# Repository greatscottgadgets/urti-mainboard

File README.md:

# URTI Mainboard

This is the open source hardware design for the mainboard of URTI, the Universal Radio Test Instrument.

https://greatscottgadgets.com/urti/

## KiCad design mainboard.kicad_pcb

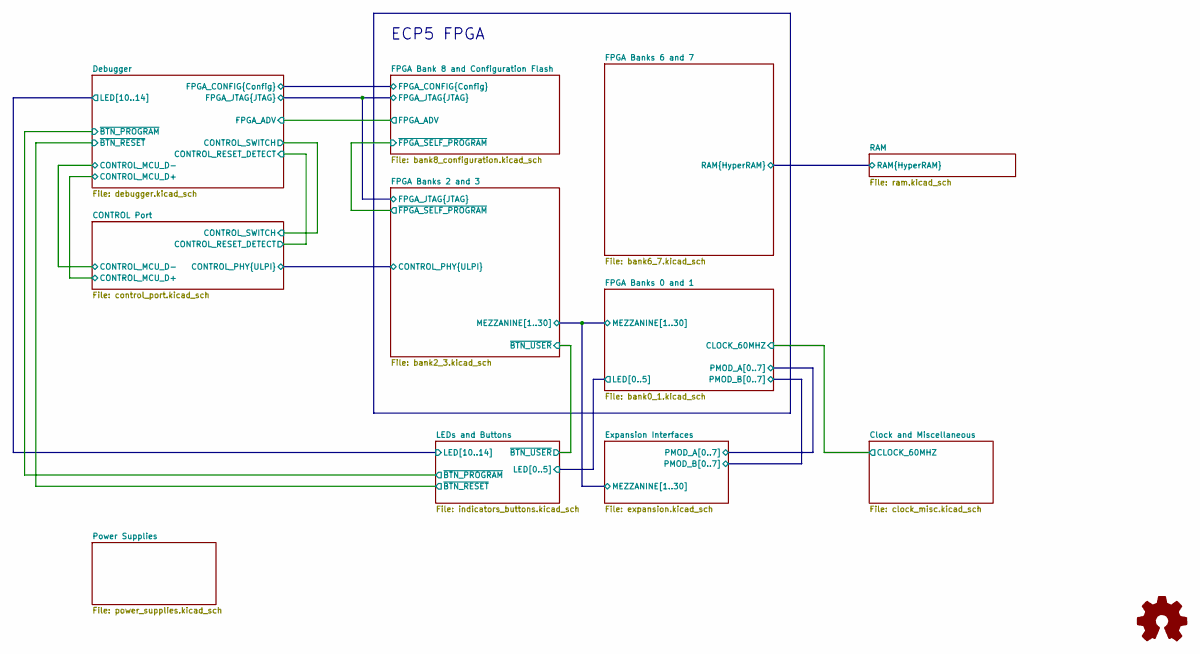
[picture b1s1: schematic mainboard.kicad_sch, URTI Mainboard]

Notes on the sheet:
ECP5 FPGA

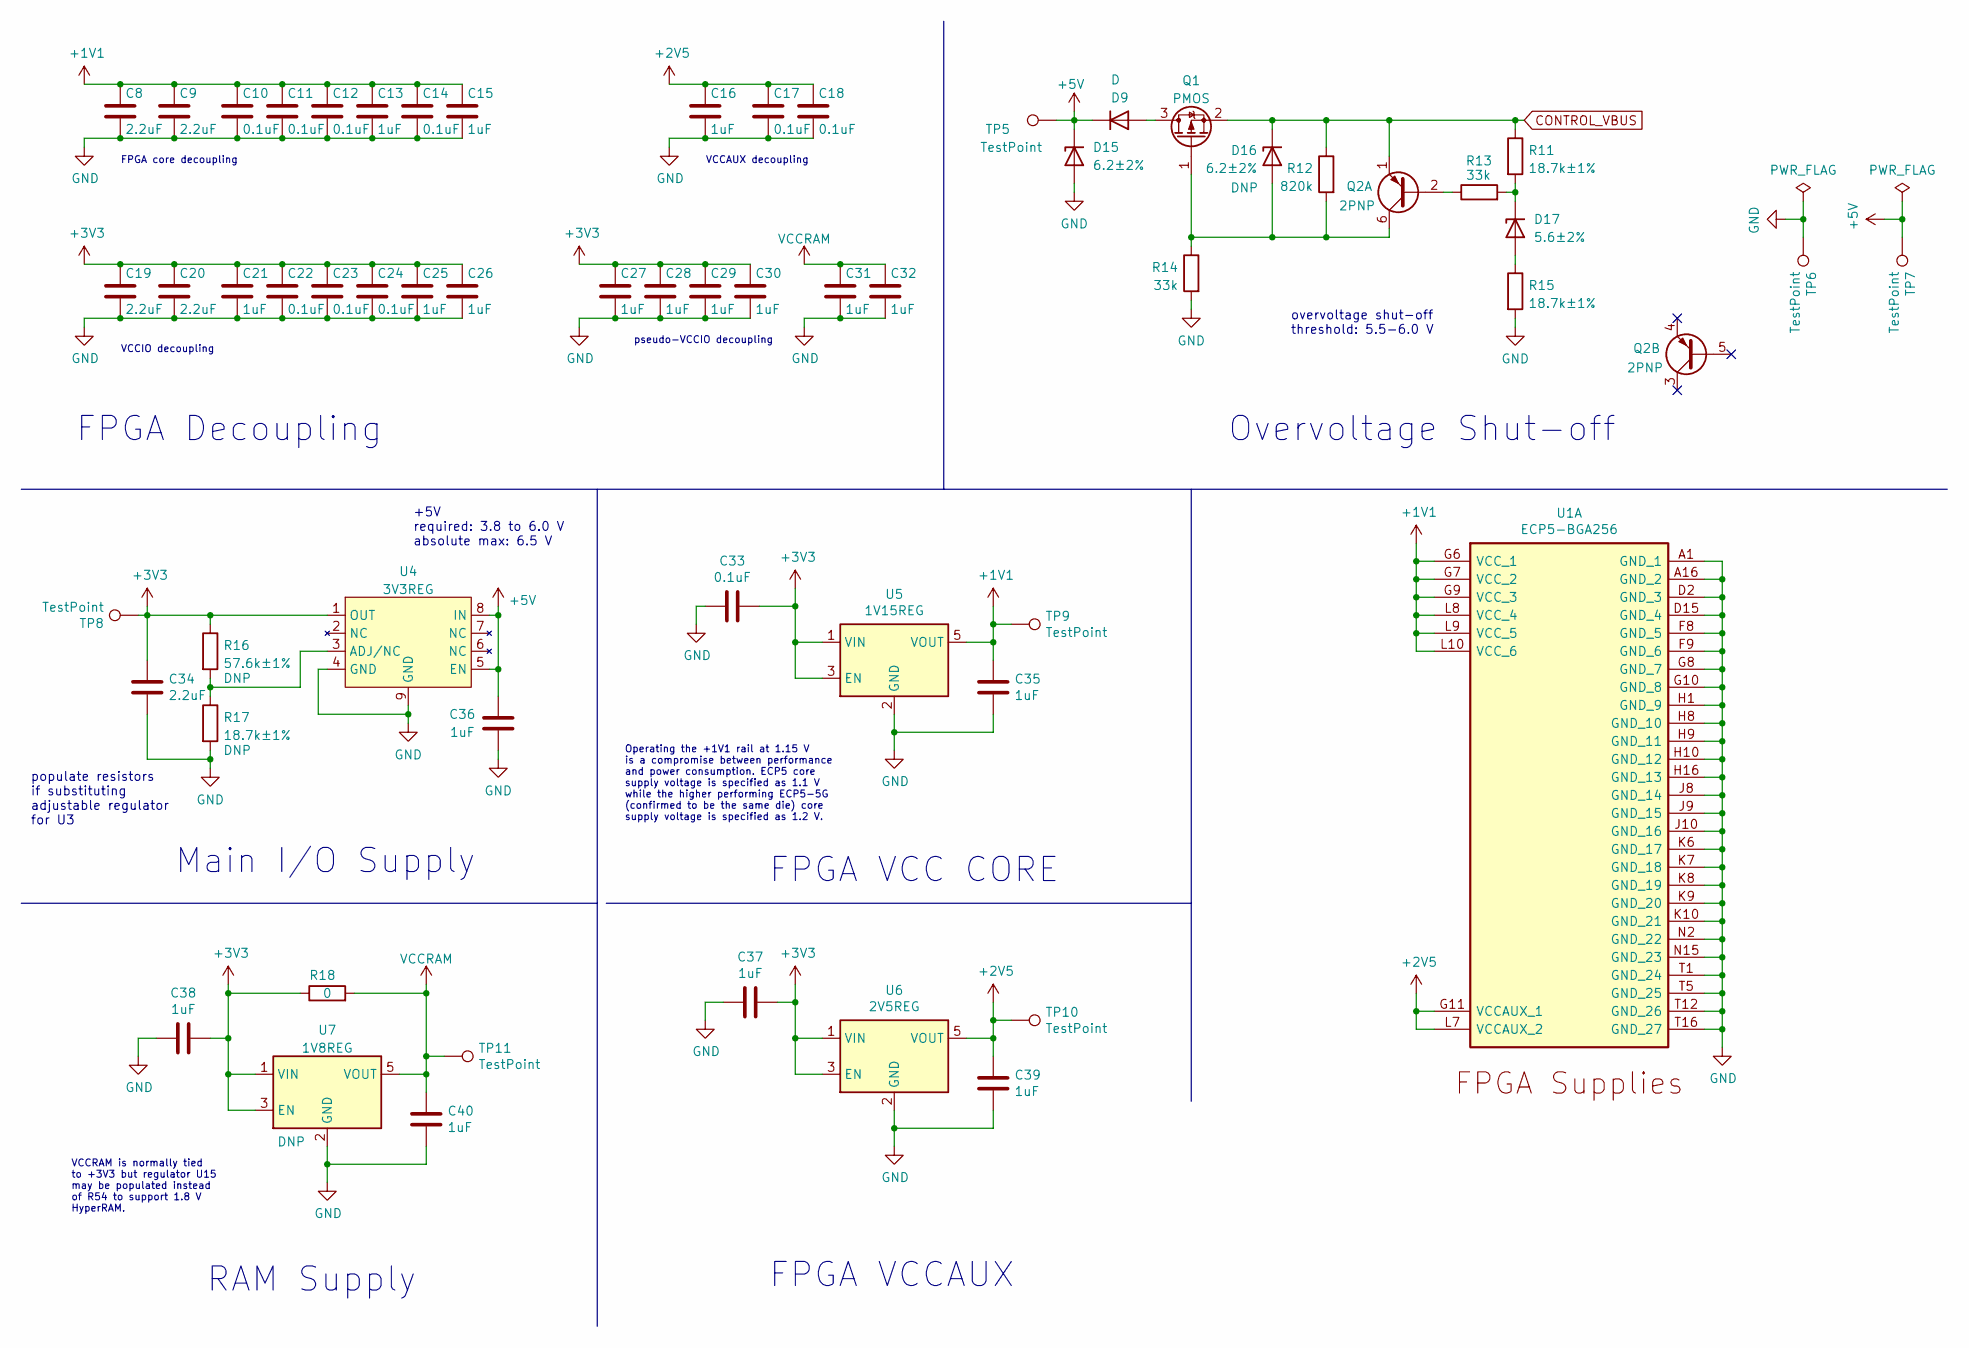
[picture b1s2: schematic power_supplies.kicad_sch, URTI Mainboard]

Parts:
C8, C9, C19, C20, C34: 2.2uF; C_0603_1608Metric; Part Number CL10A225KP8NNNC
C10, C11, C12, C14, C17, C18, C22, C23, C24, C33: 0.1uF; C_0402_1005Metric; Part Number CL05A104KA5NNNC
C13, C15, C16, C21, C25, C26, C27, C28, C29, C30, C31, C32, C35, C36, C37, C38, C39, C40: 1uF; C_0402_1005Metric; Part Number CL05A105MQ5NNNC
D9: D; D_SOD-123FL; Part Number U1D
D15, D16: 6.2±2%; DFN1006-2; Part Number BZX884-B6V2,315
D17: 5.6±2%; DFN1006-2; Part Number BZX884-B5V6,315
Q1: PMOS; SOT-23-3; Part Number YJL3401A
Q2: 2PNP; SOT-363_SC-70-6; Part Number BC857BS
R11, R15, R17: 18.7k±1%; R_0402_1005Metric; Part Number ERJ-2RKF1872X
R12: 820k; R_0402_1005Metric; Part Number RC0402JR-07820KL
R13, R14: 33k; R_0402_1005Metric; Part Number ERJ-2GEJ333X
R16: 57.6k±1%; R_0402_1005Metric; Part Number RC0402FR-0757K6L
R18: 0; R_0402_1005Metric; Part Number RC0402FR-070RL
TP5, TP6, TP7, TP8, TP9, TP10, TP11: TestPoint; TestPoint_Pad_D1.0mm
U1: ECP5-BGA256; lattice_cabga256; Part Number LFE5U-12F-6BG256C
U4: 3V3REG; DFN-8-1EP_3x3mm_P0.65mm_EP1.55x2.4mm; Part Number AP7361EA-33FGE-7
U5: 1V15REG; SOT-23-5; Part Number TCR2EF115,LM(CT
U6: 2V5REG; SOT-23-5; Part Number MIC5504-2.5YM5-TR
U7: 1V8REG; SOT-23-5; Part Number MIC5504-1.8YM5-TR

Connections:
+1V1: C8.1, C9.1, C10.1, C11.1, C12.1, C13.1, C14.1, C15.1, C35.1, TP9.1, U1.G6 (VCC_1), U1.G7 (VCC_2), U1.G9 (VCC_3), U1.L8 (VCC_4), U1.L9 (VCC_5), U1.L10 (VCC_6), U5.5 (VOUT)
+2V5: C16.1, C17.1, C18.1, C39.1, TP10.1, U1.G11 (VCCAUX_1), U1.L7 (VCCAUX_2), U6.5 (VOUT)
+3V3: C19.1, C20.1, C21.1, C22.1, C23.1, C24.1, C25.1, C26.1, C27.1, C28.1, C29.1, C30.1, C33.1, C34.1, C37.1, C38.1, R16.1, R18.1, TP8.1, U4.1 (OUT), U5.1 (VIN), U5.3 (EN), U6.1 (VIN), U6.3 (EN), U7.1 (VIN), U7.3 (EN); also elsewhere on the board
+5V: C36.1, D9.1 (K), D15.1 (K), TP5.1, TP7.1, U4.5 (EN), U4.8 (IN); also elsewhere on the board
CONTROL_VBUS: D16.1 (K), Q1.2 (S), Q2.1 (E1), R11.1, R12.1; also elsewhere on the board
GND: C8.2, C9.2, C10.2, C11.2, C12.2, C13.2, C14.2, C15.2, C16.2, C17.2, C18.2, C19.2, C20.2, C21.2, C22.2, C23.2, C24.2, C25.2, C26.2, C27.2, C28.2, C29.2, C30.2, C31.2, C32.2, C33.2, C34.2, C35.2, C36.2, C37.2, C38.2, C39.2, C40.2, D15.2 (A), R14.2, R15.2, R17.2, TP6.1, U1.A1 (GND_1), U1.A16 (GND_2), U1.D2 (GND_3), U1.D15 (GND_4), U1.F8 (GND_5), U1.F9 (GND_6), U1.G8 (GND_7), U1.G10 (GND_8), U1.H1 (GND_9), U1.H8 (GND_10), U1.H9 (GND_11), U1.H10 (GND_12), U1.H16 (GND_13), U1.J8 (GND_14), U1.J9 (GND_15), U1.J10 (GND_16), U1.K6 (GND_17), U1.K7 (GND_18), U1.K8 (GND_19), U1.K9 (GND_20), U1.K10 (GND_21), U1.N2 (GND_22), U1.N15 (GND_23), U1.T1 (GND_24), U1.T5 (GND_25), U1.T12 (GND_26), U1.T16 (GND_27), U4.4 (GND), U4.9 (GND), U5.2 (GND), U6.2 (GND), U7.2 (GND); also elsewhere on the board
unnamed: D9.2 (A), Q1.3 (D)
unnamed: D16.2 (A), Q1.1 (G), Q2.6 (C1), R12.2, R14.1
unnamed: D17.2 (A), R15.1
unnamed: D17.1 (K), R11.2, R13.2
unnamed: Q2.2 (B1), R13.1
unnamed: R16.2, R17.1, U4.3 (ADJ/NC)
VCCRAM: C31.1, C32.1, C40.1, R18.2, TP11.1, U7.5 (VOUT); also elsewhere on the board

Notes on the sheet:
VCCIO decoupling
FPGA VCC CORE
FPGA Decoupling
FPGA core decoupling
+5V required: 3.8 to 6.0 V absolute max: 6.5 V
overvoltage shut-off threshold: 5.5-6.0 V
VCCRAM is normally tied to +3V3 but regulator U15 may be populated instead of R54 to support 1.8 V HyperRAM.
VCCAUX decoupling
FPGA VCCAUX
Main I/O Supply
Overvoltage Shut-off
populate resistors if substituting adjustable regulator for U3
RAM Supply
Operating the +1V1 rail at 1.15 V is a compromise between performance and power consumption. ECP5 core supply voltage is specified as 1.1 V while the higher performing ECP5-5G (confirmed to be the same die) core supply voltage is specified as 1.2 V.
pseudo-VCCIO decoupling

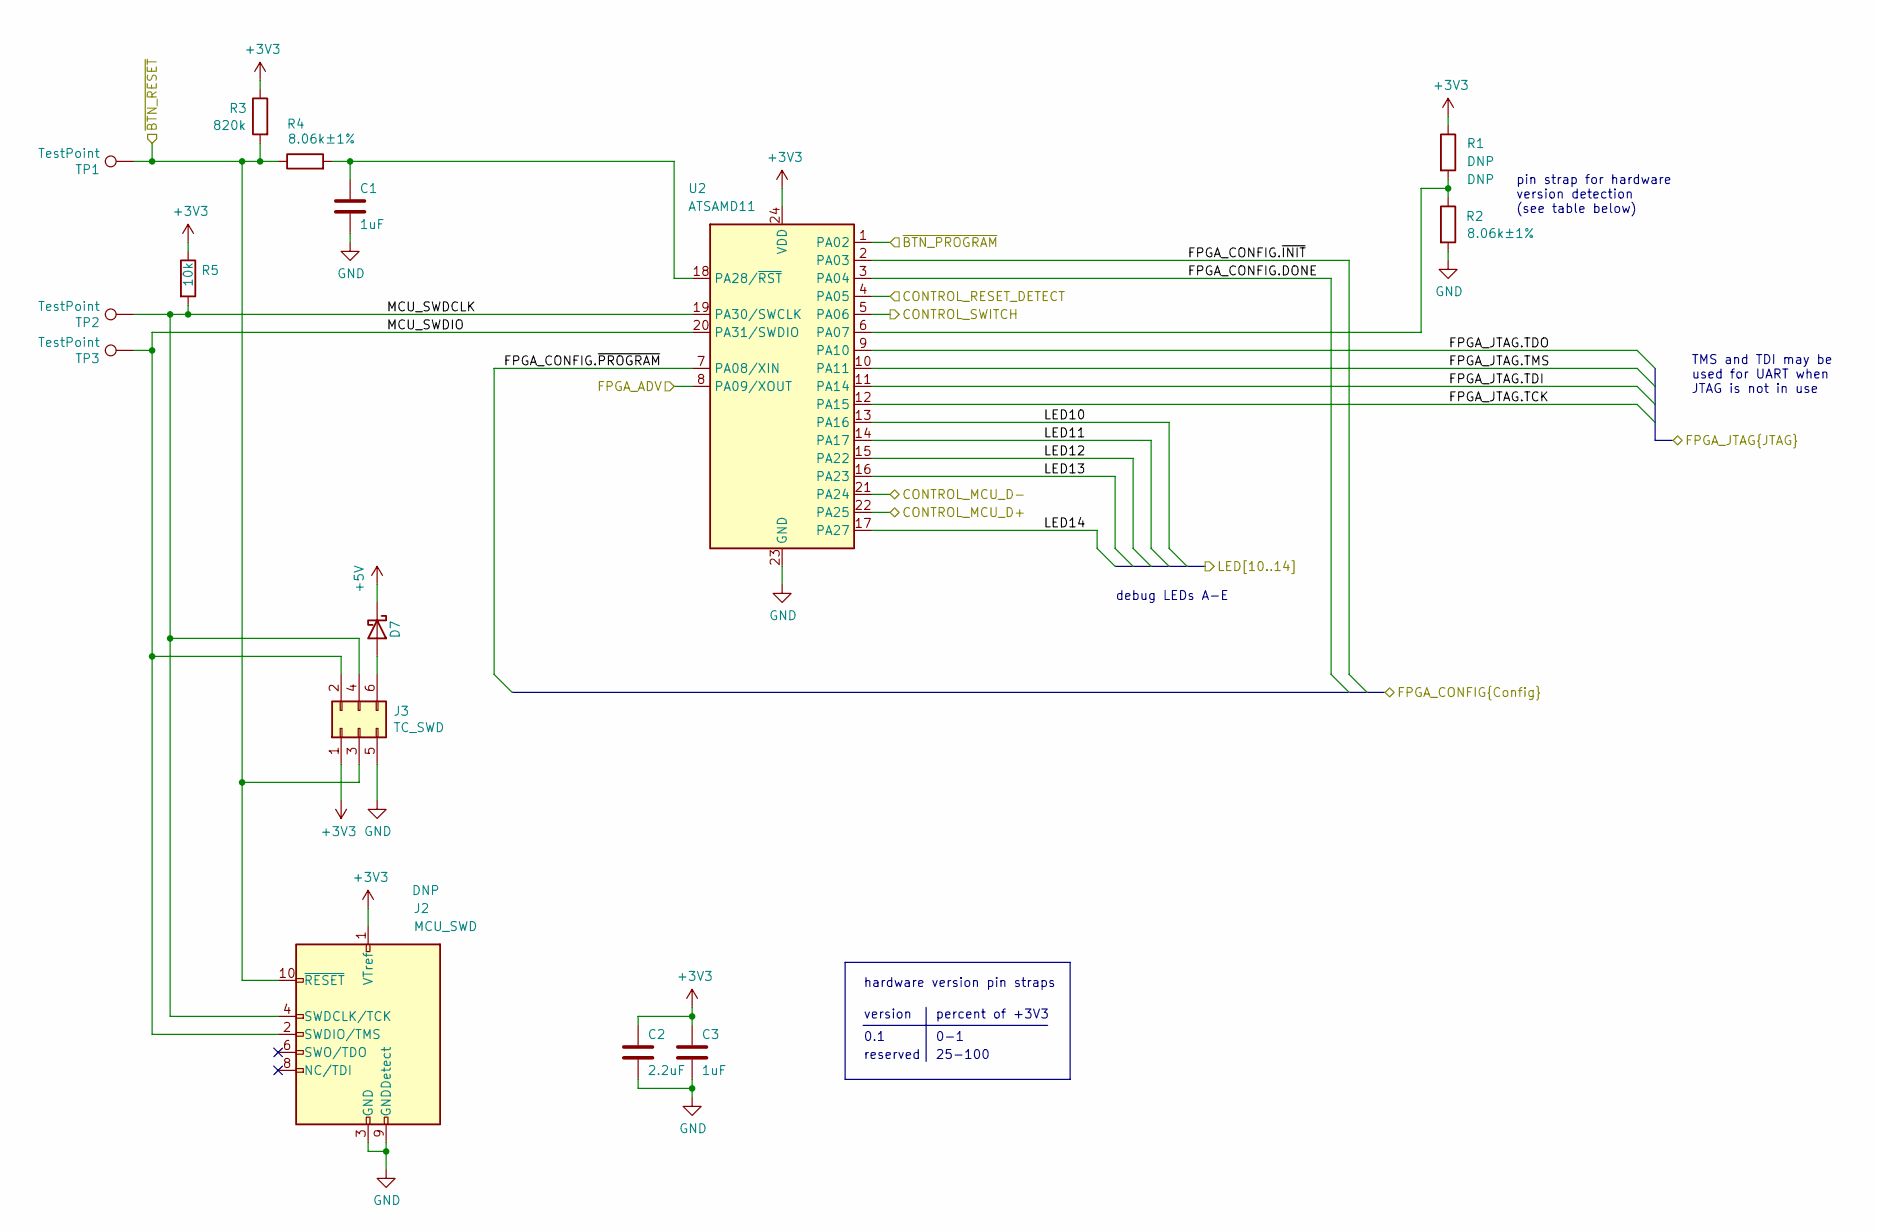
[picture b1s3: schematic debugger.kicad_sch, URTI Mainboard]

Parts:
C1, C3: 1uF; C_0402_1005Metric; Part Number CL05A105MQ5NNNC
C2: 2.2uF; C_0603_1608Metric; Part Number CL10A225KP8NNNC
D7: SCHOTTKY; DSN1006-2; Part Number PMEG4010ESBYL
J2: MCU_SWD; SWD_CONNECTOR_LARGE_BOX; Part Number FTSH-105-01-F-D-K
J3: TC_SWD; Tag-Connect_TC2030-IDC-FP_2x03_P1.27mm_Vertical; Part Number TC2030-CTX
R1: DNP; R_0402_1005Metric
R2, R4: 8.06k±1%; R_0402_1005Metric; Part Number ERJ-2RKF8061X
R3: 820k; R_0402_1005Metric; Part Number RC0402JR-07820KL
R5: 10k; R_0402_1005Metric; Part Number RC0402JR-0710KL
TP1, TP2, TP3: TestPoint; TestPoint_Pad_D1.0mm
U2: ATSAMD11; QFN-24-1EP_4x4mm_P0.5mm_EP2.6x2.6mm; Part Number ATSAMD11D14A-MUT

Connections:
+3V3: C2.1, C3.1, J2.1 (VTref), J3.1, R1.1, R3.1, R5.1, U2.24 (VDD); also elsewhere on the board
+5V: D7.1 (K); also elsewhere on the board
/CONTROL Port/CONTROL_MCU_D+: U2.22 (PA25); also elsewhere on the board
/CONTROL Port/CONTROL_MCU_D-: U2.21 (PA24); also elsewhere on the board
/CONTROL Port/CONTROL_RESET_DETECT: U2.4 (PA05); also elsewhere on the board
/CONTROL Port/CONTROL_SWITCH: U2.5 (PA06); also elsewhere on the board
/Debugger/FPGA_ADV: U2.8 (PA09/XOUT); also elsewhere on the board
/Debugger/FPGA_CONFIG.DONE: U2.3 (PA04); also elsewhere on the board
/Debugger/FPGA_CONFIG.~INIT: U2.2 (PA03); also elsewhere on the board
/Debugger/FPGA_CONFIG.~PROGRAM: U2.7 (PA08/XIN); also elsewhere on the board
/Debugger/FPGA_JTAG.TCK: U2.12 (PA15); also elsewhere on the board
/Debugger/FPGA_JTAG.TDI: U2.11 (PA14); also elsewhere on the board
/Debugger/FPGA_JTAG.TDO: U2.9 (PA10); also elsewhere on the board
/Debugger/FPGA_JTAG.TMS: U2.10 (PA11); also elsewhere on the board
/Debugger/LED10: U2.13 (PA16); also elsewhere on the board
/Debugger/LED11: U2.14 (PA17); also elsewhere on the board
/Debugger/LED12: U2.15 (PA22); also elsewhere on the board
/Debugger/LED13: U2.16 (PA23); also elsewhere on the board
/Debugger/LED14: U2.17 (PA27); also elsewhere on the board
/Debugger/MCU_SWDCLK: J2.4 (SWDCLK/TCK), J3.4, R5.2, TP2.1, U2.19 (PA30/SWCLK)
/Debugger/MCU_SWDIO: J2.2 (SWDIO/TMS), J3.2, TP3.1, U2.20 (PA31/SWDIO)
/Debugger/~BTN_PROGRAM: U2.1 (PA02); also elsewhere on the board
/Debugger/~BTN_RESET: J2.10 (~RESET), J3.3, R3.2, R4.1, TP1.1; also elsewhere on the board
GND: C1.2, C2.2, C3.2, J2.3 (GND), J2.5 (GND), J2.9 (GNDDetect), J3.5, R2.2, U2.23 (GND); also elsewhere on the board
unnamed: D7.2 (A), J3.6
unnamed: R1.2, R2.1, U2.6 (PA07)
unnamed: C1.1, R4.2, U2.18 (PA28/~RST)

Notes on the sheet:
debug LEDs A-E
reserved
25-100
version
percent of +3V3
TMS and TDI may be used for UART when JTAG is not in use
0.1
0-1
pin strap for hardware version detection (see table below)
hardware version pin straps

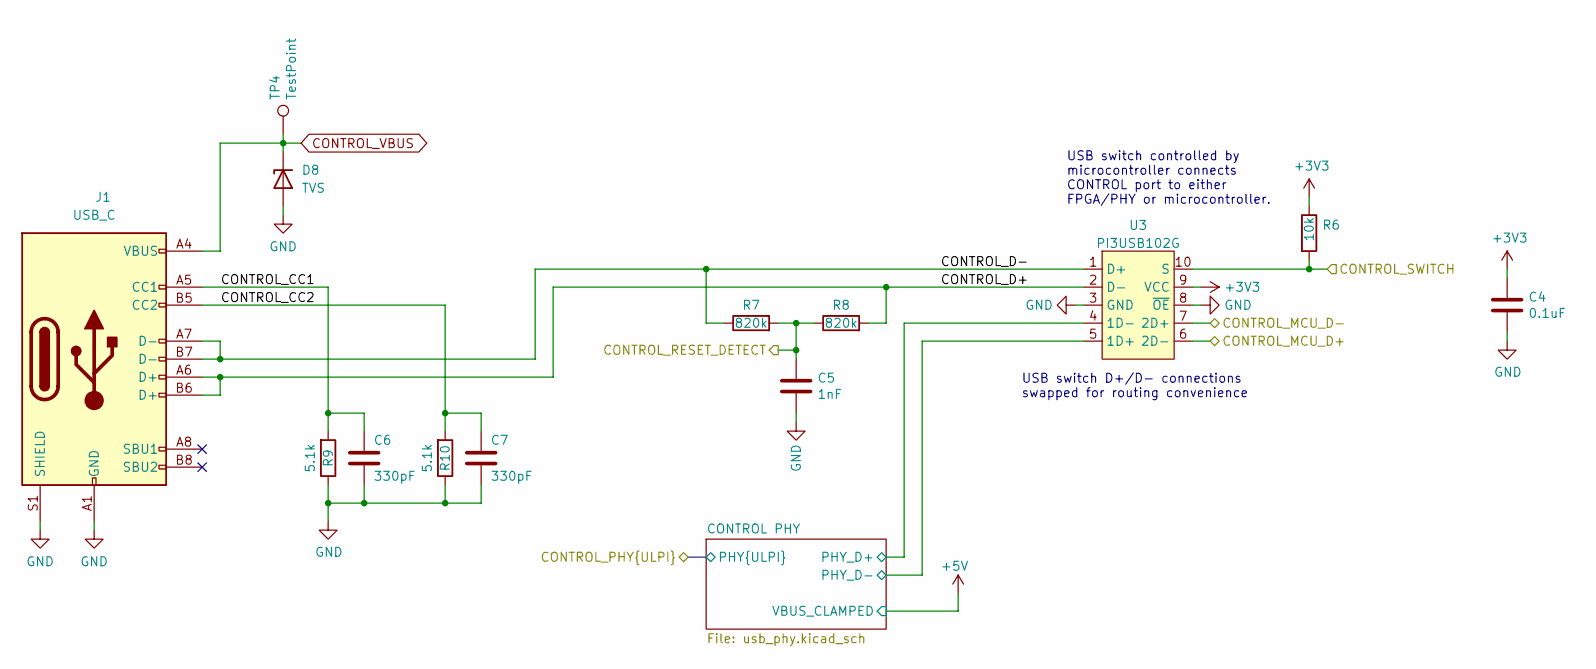
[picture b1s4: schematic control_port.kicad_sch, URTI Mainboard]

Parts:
C4: 0.1uF; C_0402_1005Metric; Part Number CL05A104KA5NNNC
C5: 1nF; C_0402_1005Metric; Part Number CL05B102KB5NNNC
C6, C7: 330pF; C_0402_1005Metric; Part Number CL05C331JB5NNNC
D8: TVS; DFN1006-2; Part Number PESD36VS1UL,315
J1: USB_C; USB_C_Receptacle_HRO_TYPE-C-31-M-12; Part Number USB-TYPE-C-019
R6: 10k; R_0402_1005Metric; Part Number RC0402JR-0710KL
R7, R8: 820k; R_0402_1005Metric; Part Number RC0402JR-07820KL
R9, R10: 5.1k; R_0402_1005Metric; Part Number RC0402JR-075K1L
TP4: TestPoint; TestPoint_Pad_D1.0mm
U3: PI3USB102G; Diodes_10-TQFN_ZL; Part Number PI3USB102GZLEX

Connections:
+3V3: C4.1, R6.1, U3.9 (VCC); also elsewhere on the board
/CONTROL Port/CONTROL PHY/PHY_D+: U3.4 (1D-); also elsewhere on the board
/CONTROL Port/CONTROL PHY/PHY_D-: U3.5 (1D+); also elsewhere on the board
/CONTROL Port/CONTROL_CC1: C6.1, J1.A5 (CC1), R9.2
/CONTROL Port/CONTROL_CC2: C7.1, J1.B5 (CC2), R10.2
/CONTROL Port/CONTROL_D+: J1.A6 (D+), J1.B6 (D+), R8.2, U3.2 (D-)
/CONTROL Port/CONTROL_D-: J1.A7 (D-), J1.B7 (D-), R7.1, U3.1 (D+)
/CONTROL Port/CONTROL_MCU_D+: U3.6 (2D-); also elsewhere on the board
/CONTROL Port/CONTROL_MCU_D-: U3.7 (2D+); also elsewhere on the board
/CONTROL Port/CONTROL_RESET_DETECT: C5.1, R7.2, R8.1; also elsewhere on the board
/CONTROL Port/CONTROL_SWITCH: R6.2, U3.10 (S); also elsewhere on the board
CONTROL_VBUS: D8.1 (K), J1.A4 (VBUS), J1.A9 (VBUS), J1.B4 (VBUS), J1.B9 (VBUS), TP4.1; also elsewhere on the board
GND: C4.2, C5.2, C6.2, C7.2, D8.2 (A), J1.A1 (GND), J1.A12 (GND), J1.B1 (GND), J1.B12 (GND), J1.S1 (SHIELD), R9.1, R10.1, U3.3 (GND), U3.8 (~OE); also elsewhere on the board

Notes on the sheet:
USB switch controlled by microcontroller connects CONTROL port to either FPGA/PHY or microcontroller.
USB switch D+/D- connections swapped for routing convenience

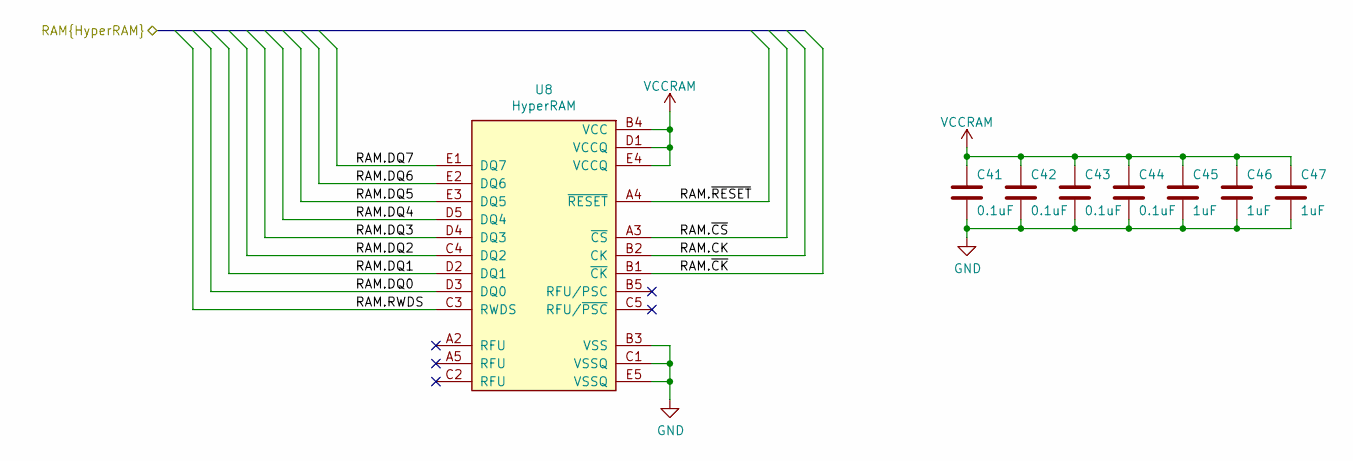
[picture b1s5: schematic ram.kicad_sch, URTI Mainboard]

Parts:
C41, C42, C43, C44: 0.1uF; C_0402_1005Metric; Part Number CL05A104KA5NNNC
C45, C46, C47: 1uF; C_0402_1005Metric; Part Number CL05A105MQ5NNNC
U8: HyperRAM; BGA-24_5x5_6.0x8.0mm; Part Number W956A8MBYA6I

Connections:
/FPGA Banks 6 and 7/RAM.CK: U8.B2 (CK); also elsewhere on the board
/FPGA Banks 6 and 7/RAM.DQ0: U8.D3 (DQ0); also elsewhere on the board
/FPGA Banks 6 and 7/RAM.DQ1: U8.D2 (DQ1); also elsewhere on the board
/FPGA Banks 6 and 7/RAM.DQ2: U8.C4 (DQ2); also elsewhere on the board
/FPGA Banks 6 and 7/RAM.DQ3: U8.D4 (DQ3); also elsewhere on the board
/FPGA Banks 6 and 7/RAM.DQ4: U8.D5 (DQ4); also elsewhere on the board
/FPGA Banks 6 and 7/RAM.DQ5: U8.E3 (DQ5); also elsewhere on the board
/FPGA Banks 6 and 7/RAM.DQ6: U8.E2 (DQ6); also elsewhere on the board
/FPGA Banks 6 and 7/RAM.DQ7: U8.E1 (DQ7); also elsewhere on the board
/FPGA Banks 6 and 7/RAM.RWDS: U8.C3 (RWDS); also elsewhere on the board
/FPGA Banks 6 and 7/RAM.~CK: U8.B1 (~CK); also elsewhere on the board
/FPGA Banks 6 and 7/RAM.~CS: U8.A3 (~CS); also elsewhere on the board
/FPGA Banks 6 and 7/RAM.~RESET: U8.A4 (~RESET); also elsewhere on the board
GND: C41.2, C42.2, C43.2, C44.2, C45.2, C46.2, C47.2, U8.B3 (VSS), U8.C1 (VSSQ), U8.E5 (VSSQ); also elsewhere on the board
VCCRAM: C41.1, C42.1, C43.1, C44.1, C45.1, C46.1, C47.1, U8.B4 (VCC), U8.D1 (VCCQ), U8.E4 (VCCQ); also elsewhere on the board

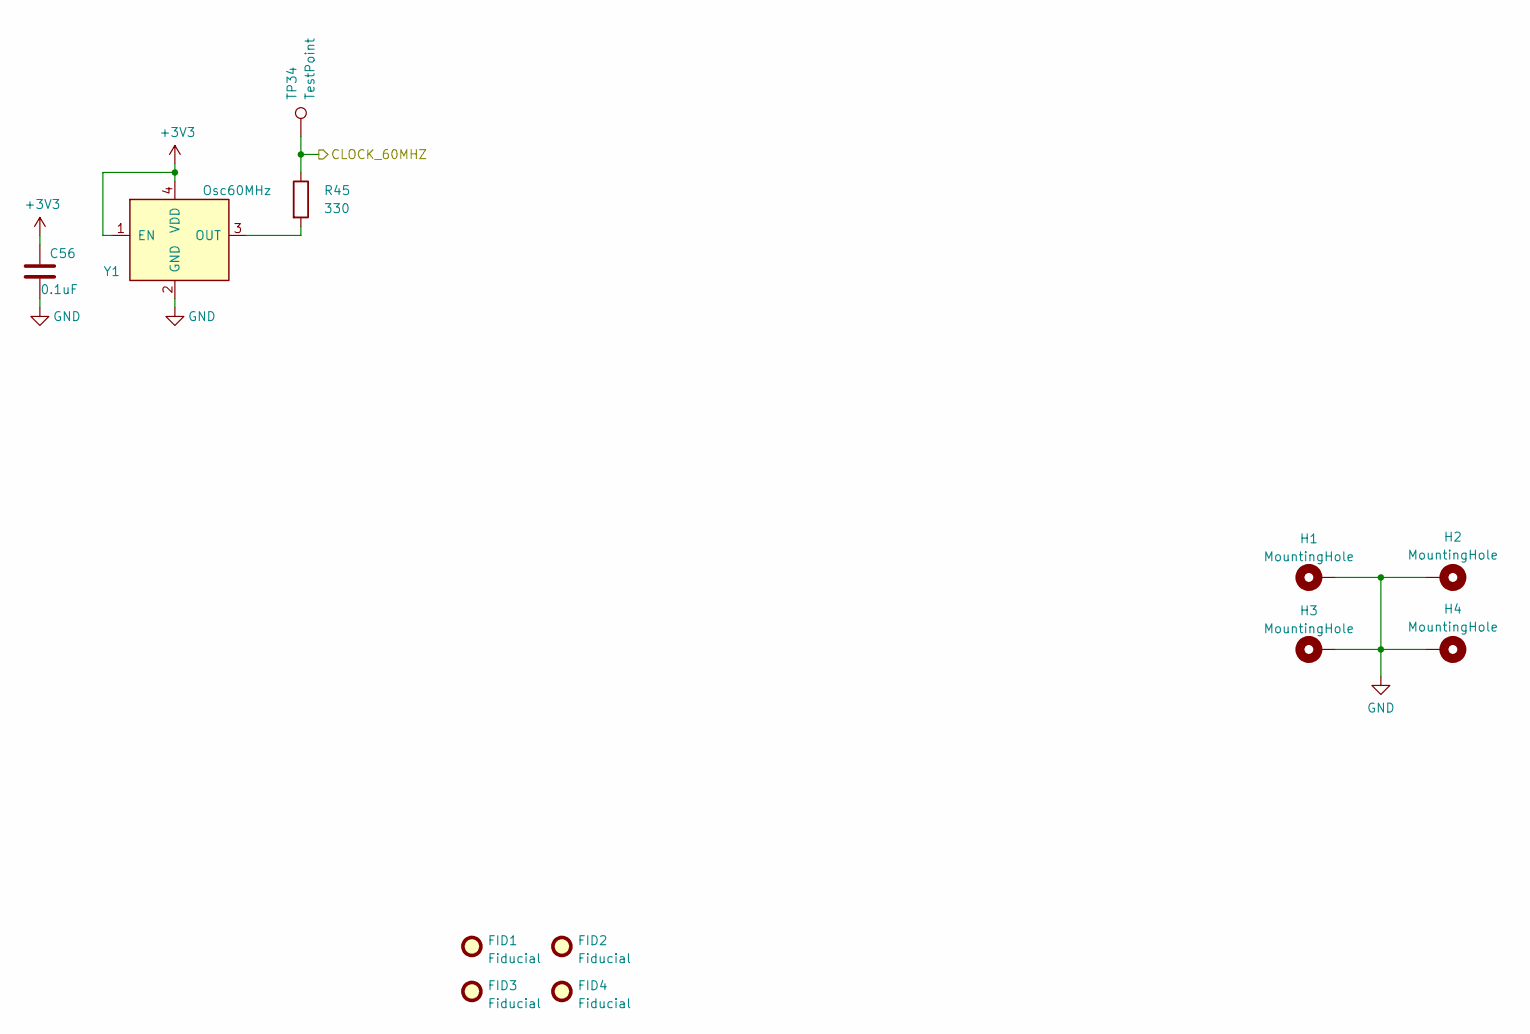
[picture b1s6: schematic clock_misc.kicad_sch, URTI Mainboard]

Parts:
C56: 0.1uF; C_0402_1005Metric; Part Number CL05A104KA5NNNC
FID1, FID2, FID3, FID4: Fiducial; Fiducial_0.5mm_Mask1mm
H1, H2, H3, H4: MountingHole; MountingHole_2.2mm_M2_Pad_Via
R45: 330; R_0402_1005Metric; Part Number RC0402FR-13330RL
TP34: TestPoint; TestPoint_Pad_D1.0mm
Y1: Osc60MHz; Crystal_SMD_3225-4Pin_3.2x2.5mm; Part Number SIT1602BC-23-33E-60.000000E

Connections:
+3V3: C56.1, Y1.1 (EN), Y1.4 (VDD); also elsewhere on the board
/Clock and Miscellaneous/CLOCK_60MHZ: R45.1, TP34.1; also elsewhere on the board
GND: C56.2, H1.1, H2.1, H3.1, H4.1, Y1.2 (GND); also elsewhere on the board
unnamed: R45.2, Y1.3 (OUT)

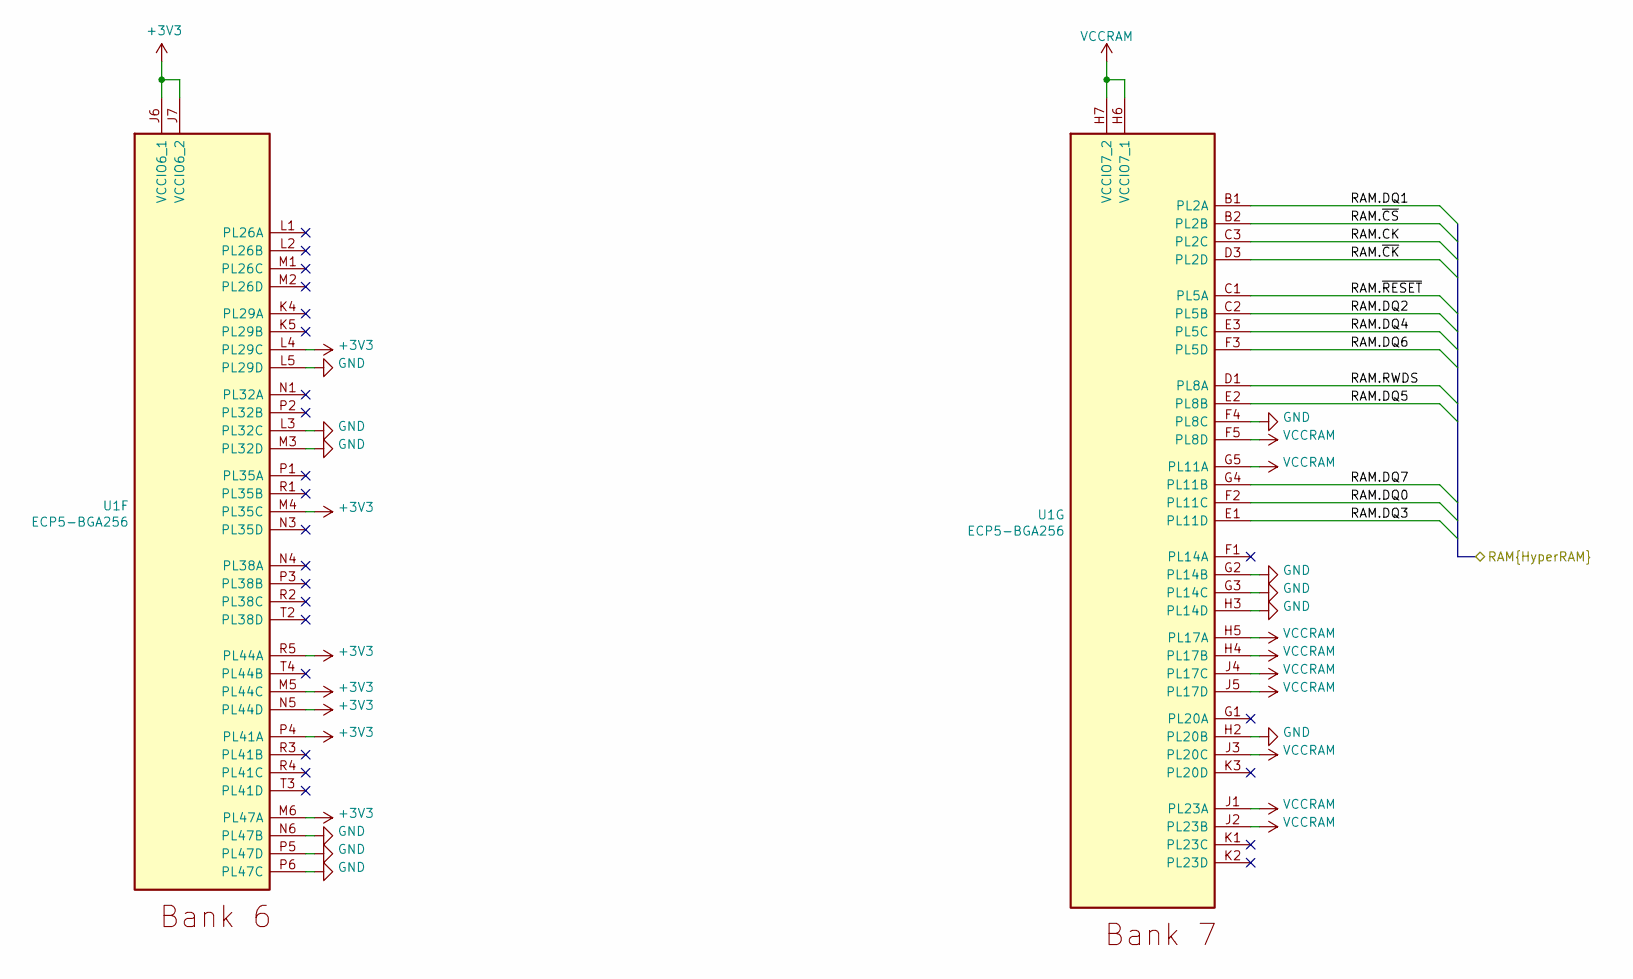
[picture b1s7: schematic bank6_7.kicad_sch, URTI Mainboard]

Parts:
U1: ECP5-BGA256; lattice_cabga256; Part Number LFE5U-12F-6BG256C

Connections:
+3V3: U1.J6 (VCCIO6_1), U1.J7 (VCCIO6_2), U1.L4 (PL29C), U1.M4 (PL35C), U1.M5 (PL44C), U1.M6 (PL47A), U1.N5 (PL44D), U1.P4 (PL41A), U1.R5 (PL44A); also elsewhere on the board
/FPGA Banks 6 and 7/RAM.CK: U1.C3 (PL2C); also elsewhere on the board
/FPGA Banks 6 and 7/RAM.DQ0: U1.F2 (PL11C); also elsewhere on the board
/FPGA Banks 6 and 7/RAM.DQ1: U1.B1 (PL2A); also elsewhere on the board
/FPGA Banks 6 and 7/RAM.DQ2: U1.C2 (PL5B); also elsewhere on the board
/FPGA Banks 6 and 7/RAM.DQ3: U1.E1 (PL11D); also elsewhere on the board
/FPGA Banks 6 and 7/RAM.DQ4: U1.E3 (PL5C); also elsewhere on the board
/FPGA Banks 6 and 7/RAM.DQ5: U1.E2 (PL8B); also elsewhere on the board
/FPGA Banks 6 and 7/RAM.DQ6: U1.F3 (PL5D); also elsewhere on the board
/FPGA Banks 6 and 7/RAM.DQ7: U1.G4 (PL11B); also elsewhere on the board
/FPGA Banks 6 and 7/RAM.RWDS: U1.D1 (PL8A); also elsewhere on the board
/FPGA Banks 6 and 7/RAM.~CK: U1.D3 (PL2D); also elsewhere on the board
/FPGA Banks 6 and 7/RAM.~CS: U1.B2 (PL2B); also elsewhere on the board
/FPGA Banks 6 and 7/RAM.~RESET: U1.C1 (PL5A); also elsewhere on the board
GND: U1.F4 (PL8C), U1.G2 (PL14B), U1.G3 (PL14C), U1.H2 (PL20B), U1.H3 (PL14D), U1.L3 (PL32C), U1.L5 (PL29D), U1.M3 (PL32D), U1.N6 (PL47B), U1.P5 (PL47D), U1.P6 (PL47C); also elsewhere on the board
VCCRAM: U1.F5 (PL8D), U1.G5 (PL11A), U1.H4 (PL17B), U1.H5 (PL17A), U1.H6 (VCCIO7_1), U1.H7 (VCCIO7_2), U1.J1 (PL23A), U1.J2 (PL23B), U1.J3 (PL20C), U1.J4 (PL17C), U1.J5 (PL17D); also elsewhere on the board

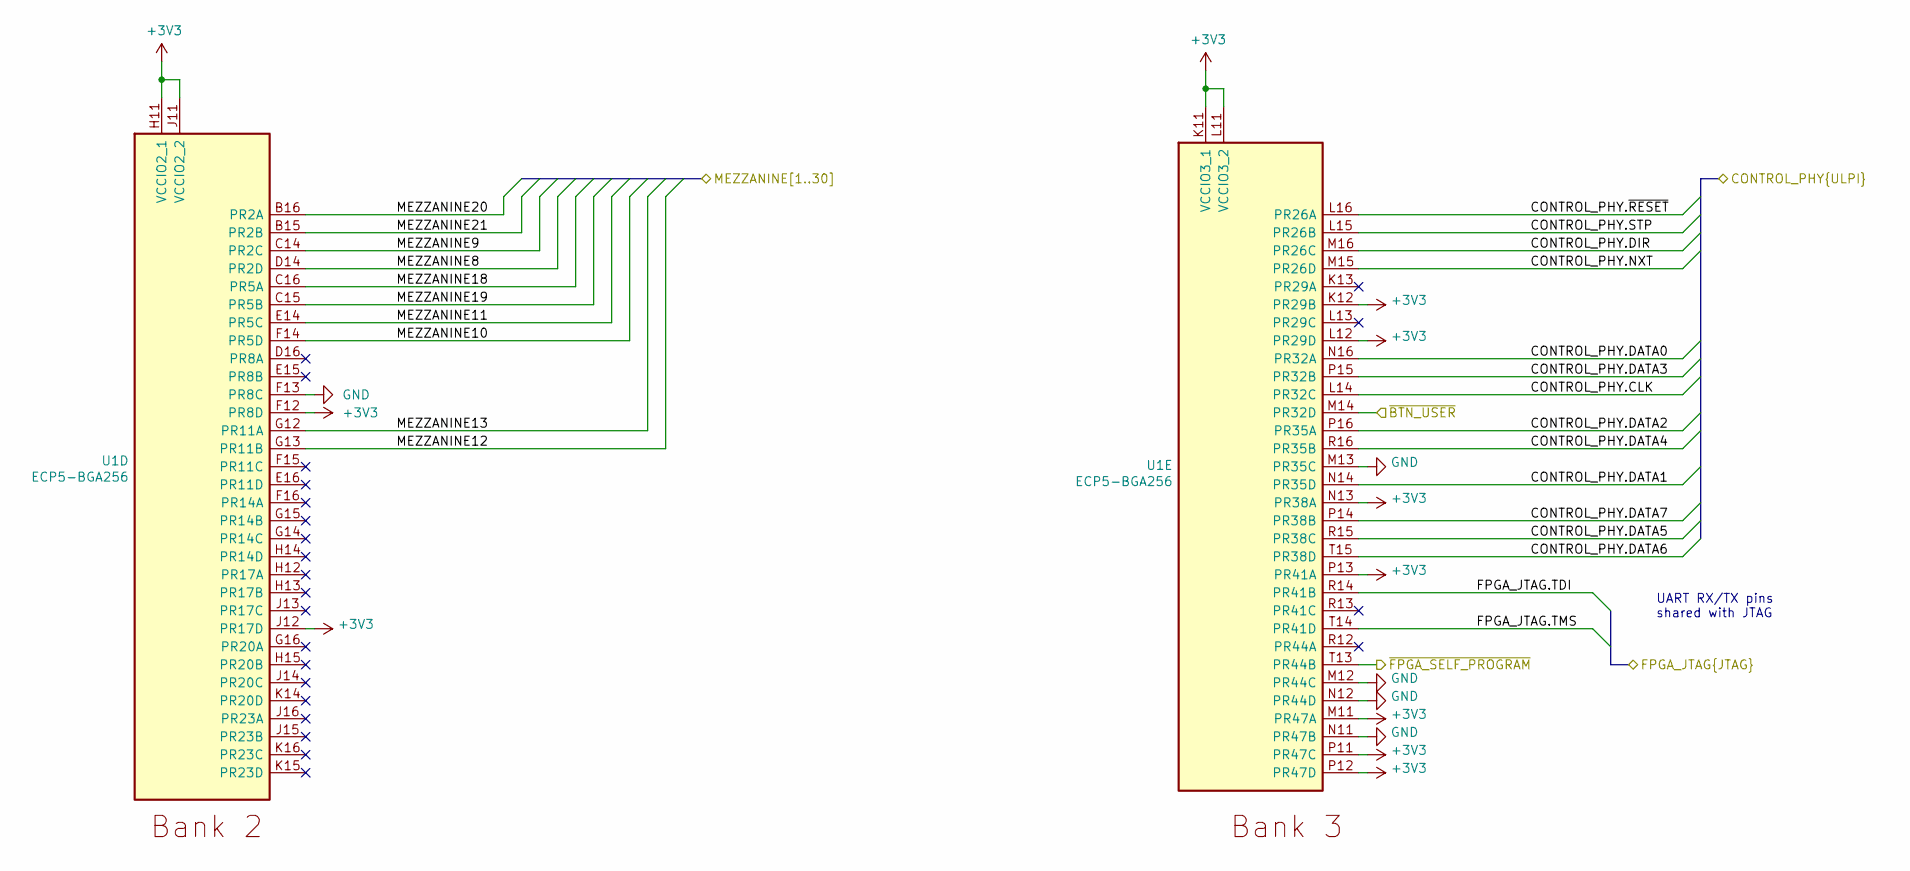
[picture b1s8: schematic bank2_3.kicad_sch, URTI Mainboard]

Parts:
U1: ECP5-BGA256; lattice_cabga256; Part Number LFE5U-12F-6BG256C

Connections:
+3V3: U1.F12 (PR8D), U1.H11 (VCCIO2_1), U1.J11 (VCCIO2_2), U1.J12 (PR17D), U1.K11 (VCCIO3_1), U1.K12 (PR29B), U1.L11 (VCCIO3_2), U1.L12 (PR29D), U1.M11 (PR47A), U1.N13 (PR38A), U1.P11 (PR47C), U1.P12 (PR47D), U1.P13 (PR41A); also elsewhere on the board
/CONTROL Port/CONTROL_PHY.CLK: U1.L14 (PR32C); also elsewhere on the board
/CONTROL Port/CONTROL_PHY.DATA0: U1.N16 (PR32A); also elsewhere on the board
/CONTROL Port/CONTROL_PHY.DATA1: U1.N14 (PR35D); also elsewhere on the board
/CONTROL Port/CONTROL_PHY.DATA2: U1.P16 (PR35A); also elsewhere on the board
/CONTROL Port/CONTROL_PHY.DATA3: U1.P15 (PR32B); also elsewhere on the board
/CONTROL Port/CONTROL_PHY.DATA4: U1.R16 (PR35B); also elsewhere on the board
/CONTROL Port/CONTROL_PHY.DATA5: U1.R15 (PR38C); also elsewhere on the board
/CONTROL Port/CONTROL_PHY.DATA6: U1.T15 (PR38D); also elsewhere on the board
/CONTROL Port/CONTROL_PHY.DATA7: U1.P14 (PR38B); also elsewhere on the board
/CONTROL Port/CONTROL_PHY.DIR: U1.M16 (PR26C); also elsewhere on the board
/CONTROL Port/CONTROL_PHY.NXT: U1.M15 (PR26D); also elsewhere on the board
/CONTROL Port/CONTROL_PHY.STP: U1.L15 (PR26B); also elsewhere on the board
/CONTROL Port/CONTROL_PHY.~RESET: U1.L16 (PR26A); also elsewhere on the board
/Debugger/FPGA_JTAG.TDI: U1.R14 (PR41B); also elsewhere on the board
/Debugger/FPGA_JTAG.TMS: U1.T14 (PR41D); also elsewhere on the board
/Expansion Interfaces/MEZZANINE8: U1.D14 (PR2D); also elsewhere on the board
/Expansion Interfaces/MEZZANINE9: U1.C14 (PR2C); also elsewhere on the board
/Expansion Interfaces/MEZZANINE10: U1.F14 (PR5D); also elsewhere on the board
/Expansion Interfaces/MEZZANINE11: U1.E14 (PR5C); also elsewhere on the board
/Expansion Interfaces/MEZZANINE12: U1.G13 (PR11B); also elsewhere on the board
/Expansion Interfaces/MEZZANINE13: U1.G12 (PR11A); also elsewhere on the board
/Expansion Interfaces/MEZZANINE18: U1.C16 (PR5A); also elsewhere on the board
/Expansion Interfaces/MEZZANINE19: U1.C15 (PR5B); also elsewhere on the board
/Expansion Interfaces/MEZZANINE20: U1.B16 (PR2A); also elsewhere on the board
/Expansion Interfaces/MEZZANINE21: U1.B15 (PR2B); also elsewhere on the board
/FPGA Bank 8 and Configuration Flash/~FPGA_SELF_PROGRAM: U1.T13 (PR44B); also elsewhere on the board
/FPGA Banks 2 and 3/~BTN_USER: U1.M14 (PR32D); also elsewhere on the board
GND: U1.F13 (PR8C), U1.M12 (PR44C), U1.M13 (PR35C), U1.N11 (PR47B), U1.N12 (PR44D); also elsewhere on the board

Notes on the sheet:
UART RX/TX pins shared with JTAG

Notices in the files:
bank0_1.kicad_sch:
Copyright 2023 Great Scott Gadgets
Licensed under the CERN-OHL-P v2
